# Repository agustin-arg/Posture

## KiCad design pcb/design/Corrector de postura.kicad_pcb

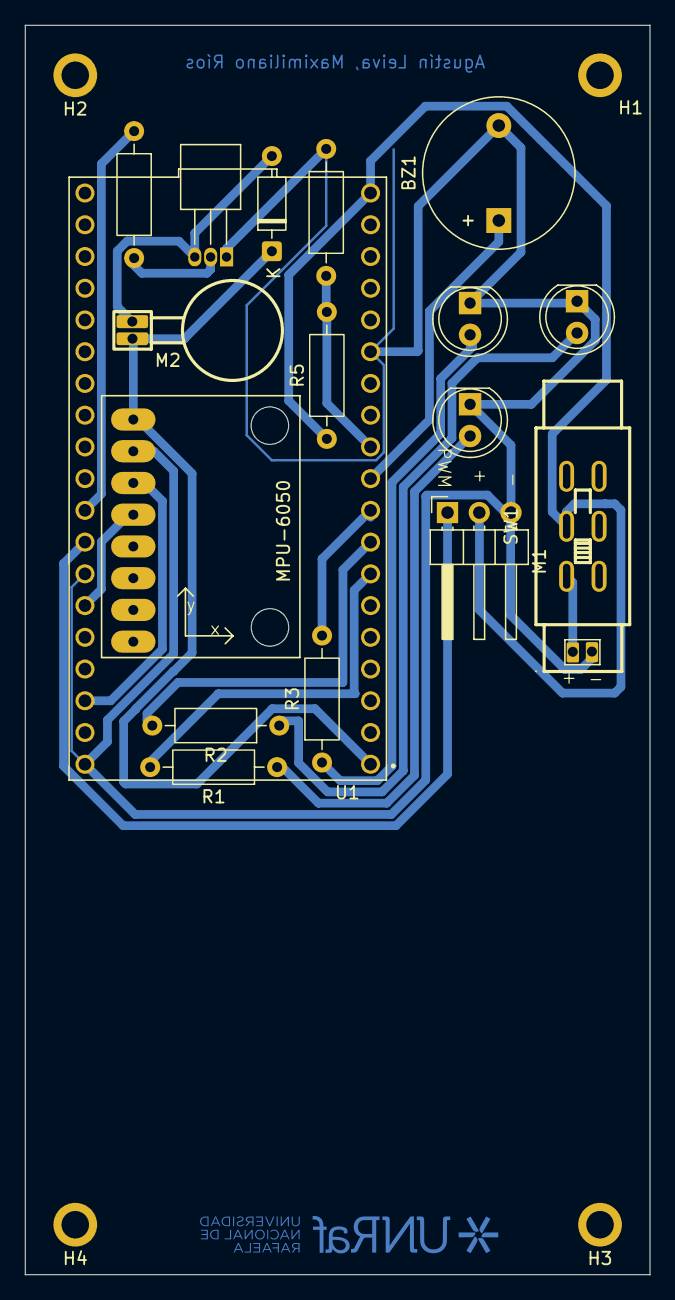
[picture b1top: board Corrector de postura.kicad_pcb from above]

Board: 2 copper layers, 50.0 x 100.0 mm, 22 parts (0 on the bottom side), 18 nets.

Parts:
BT1: Battery; SolderJumper-2_P1.3mm_Open_Pad1.0x1.5mm
BZ1: Buzzer; Buzzer_12x9.5RM7.6
D4: 1N4148; D_DO-35_SOD27_P7.62mm_Horizontal
H1: H1; MountingHole_2.2mm_M2_ISO7380_Pad
H2, H3, H4: MountingHole_2.2mm_M2_ISO7380_Pad
L1: LED Blue; LED_D5.0mm_Clear
L2: LED Green; LED_D5.0mm_Clear
L3: LED Red; LED_D5.0mm_Clear
M1: Motor_Servo; PinHeader_1x03_P2.54mm_Horizontal
M2: Motor_ERM; motor
Q1: PN2222A; TO-92_Inline_Horizontal1
R1, R2, R3: 220Ω; R_Axial_DIN0207_L6.3mm_D2.5mm_P10.16mm_Horizontal
R4: 470Ω; R_Axial_DIN0207_L6.3mm_D2.5mm_P10.16mm_Horizontal
R5, R6: 100kΩ; R_Axial_DIN0207_L6.3mm_D2.5mm_P10.16mm_Horizontal
SW1: SW_SPST; SW-TH_SS-22F25-G050
U1: NODEMCU-32S; MODULE_NODEMCU-32S
U2: GY-521

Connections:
/3.3V-J1_1: D4.1 (K), M2.1 (+), U1.J1_1 (3.3V), U2.VCC
/IO27-J1_11: R5.2, R6.1, U1.J1_11 (IO27)
GND: BT1.2 (-), BZ1.2 (-), L1.1 (K), L2.1 (K), L3.1 (K), M1.3 (-), Q1.1 (E), R6.2, U1.J1_14 (GND), U1.J2_1 (GND), U1.J2_7 (GND), U2.GND
unnamed: BT1.1 (+), SW1.1 (A)
unnamed: BZ1.1 (+), U1.J1_10 (IO26)
unnamed: D4.2 (A), M2.2 (-), Q1.3 (C)
unnamed: L1.2 (A), R1.1
unnamed: L2.2 (A), R2.1
unnamed: L3.2 (A), R3.1
unnamed: M1.2 (+), R5.1, SW1.2 (B), U1.J1_19 (5V)
unnamed: M1.1 (PWM), U1.J2_8 (IO19)
unnamed: Q1.2 (B), R4.2
unnamed: R4.1, U1.J2_9 (IO18)
unnamed: U1.J2_6 (IO21), U2.SDA
unnamed: U1.J2_3 (IO22), U2.SCL
unnamed: R3.2, U1.J1_9 (IO25)
unnamed: R1.2, U1.J1_7 (IO32)
unnamed: R2.2, U1.J1_8 (IO33)

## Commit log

2026-01-04 fix: typo en actuators.py
2026-01-17 hotfix: Confianza invertida en posture_logic.py
2026-01-28 Feat: Pruebas finales
2026-01-29 Added KiCAD project designs and schematics, Onshape project enclosure and other.
2026-02-22 feat: Add pull request templates
2026-02-22 refactor: Clean up code formatting
2026-02-22 fix: - The get_battery_level(voltage) function has been moved. -notify_battery() now directly receives the `battery_level`. -The workflow has been updated: battery_monitor first reads and classifies 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
2026-02-22 feat: Add servo control characteristics and update posture logic for gyro axis
2026-02-22 feat: Enhance servo, buzzer, and vibrator control logic for improved posture feedback
2026-02-22 Fix: Update the Posture application for servo control service
2026-02-23 feat: Add test files
2026-02-27 feat: add docs files
